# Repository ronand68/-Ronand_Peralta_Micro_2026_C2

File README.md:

# -Ronand_Peralta_Micro_2026_C2

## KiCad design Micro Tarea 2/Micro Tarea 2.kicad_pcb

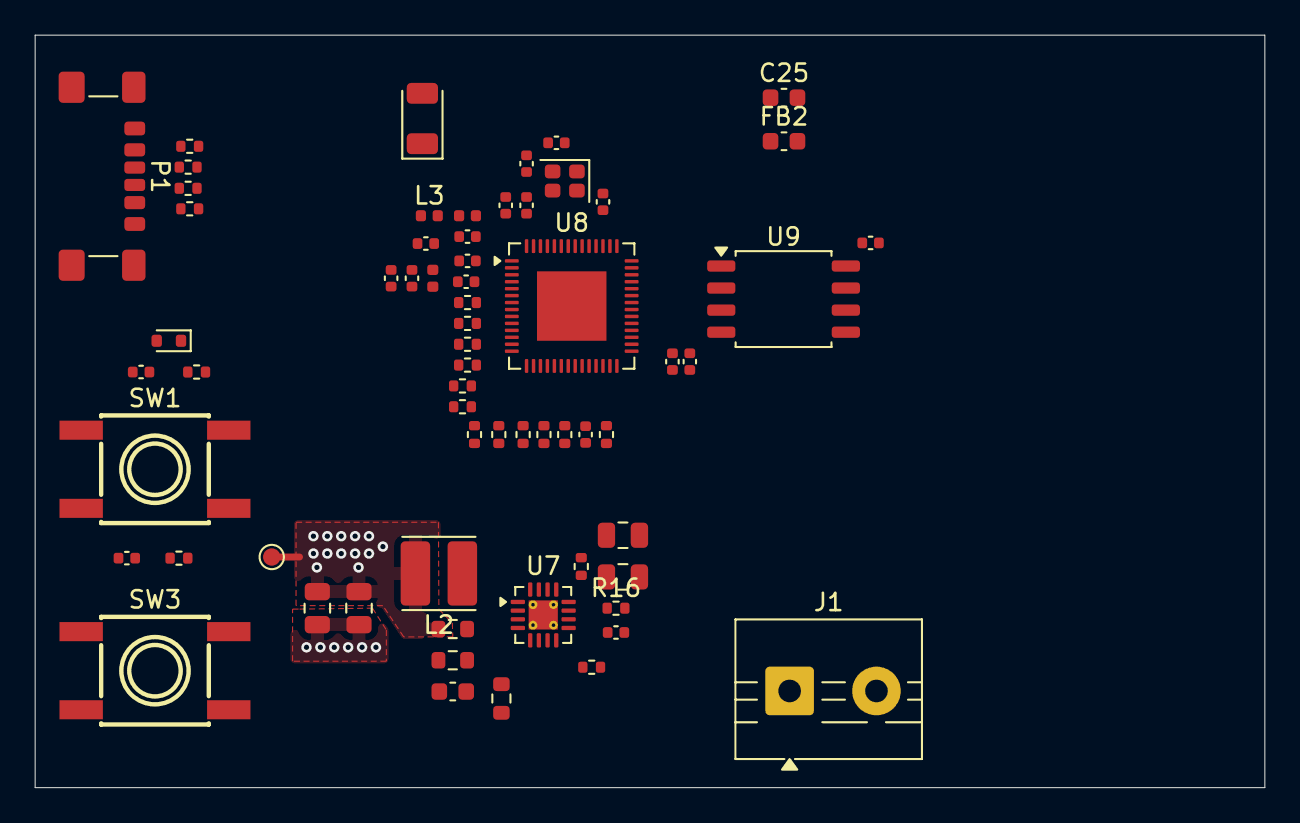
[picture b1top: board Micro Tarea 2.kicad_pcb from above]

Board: 4 copper layers, 70.8 x 43.3 mm, 64 parts (0 on the bottom side), 43 nets.

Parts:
AE1: 2450AT18A100E; Johanson_2450AT18x100
C14, C22: 22uF; C_0805_2012Metric
C15: 10uF; C_0805_2012Metric
C16: 10nF; C_0402_1005Metric
C21: 220pF; C_0603_1608Metric
C23: 100nF; C_0805_2012Metric
C24, C31, C35, C39: 1uF; C_0402_1005Metric
C25: 100nF; C_0603_1608Metric
C26, C27, C29: 12pF; C_0402_1005Metric
C28: 1.2pF; C_0402_1005Metric
C30, C32, C33, C34, C37, C38, C41: 100nF; C_0402_1005Metric
C36: 2.4pF; C_0402_1005Metric
C40: 10uF; C_0402_1005Metric
D5: LRB520S-30T1G; D_SOD-523
FB2: 120R; C_0603_1608Metric
J1: Screw_Terminal_01x02; TerminalBlock_MaiXu_MX126-5.0-02P_1x02_P5.00mm
L2: 2.2uH; L_Cenker_CKCS4020
L3: 3.3nH; L_0402_1005Metric
L4: 2.7nH; L_0402_1005Metric
L5: 2.2nH; L_0402_1005Metric
P1: USB_C_Plug_USB2.0; USB_C_Receptacle_GCT_USB4135-GF-A_6P_TopMnt_Horizontal
R2, R3: 22R; R_0402_1005Metric
R14, R15, R16: 100k; R_0402_1005Metric
R17: 49.9R; R_0603_1608Metric
R18: 68.1k; R_0603_1608Metric
R19: 22.1k; R_0603_1608Metric
R20, R21, R34, R35: 10k; R_0402_1005Metric
R22, R23, R24, R25, R26, R27, R28, R29, R30, R31: 0R; R_0402_1005Metric
R32, R33: 4.7k; R_0402_1005Metric
SW1, SW3: K2-1157SP-I4SW-04
TP6: TestPoint; TestPoint_Pad_D1.0mm
U7: TPS62130; VQFN-16-1EP_3x3mm_P0.5mm_EP1.68x1.68mm_ThermalVias
U8: ESP32-S3R8; QFN-56-1EP_7x7mm_P0.4mm_EP4x4mm
U9: W25Q128JVSIQ; SOIC-8_5.3x5.3mm_P1.27mm
Y1: 40MHz; Crystal_SMD_2016-4Pin_2.0x1.6mm

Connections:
+3V3: C22.1, C23.1, FB2.1, L2.2, R17.1, TP6.1 (1_1), U7.14 (VOS)
+5V: C14.1, C15.1, J1.1, P1.A9 (VBUS), P1.B9 (VBUS), R14.1, R15.1, R16.1, U7.10 (VIN), U7.11 (VIN), U7.12 (VIN)
/Untitled Sheet/SPI_CLK: U8.33 (SPICLK), U9.6 (CLK)
/Untitled Sheet/SPI_CS0: U8.32 (SPICS0), U9.1 (~CS)
/Untitled Sheet/SPI_D: U8.35 (SPID), U9.5 (DI/IO_{0})
/Untitled Sheet/SPI_HD: U8.30 (SPIHD), U9.7 (~HOLD/~RESET/IO_{3})
/Untitled Sheet/SPI_Q: U8.34 (SPIQ), U9.2 (DO/IO_{1})
/Untitled Sheet/SPI_WP: U8.31 (SPIWP), U9.3 (~WP/IO_{2})
ESP_3V3: C25.1, C30.1, C31.2, C32.2, C33.1, C34.1, C35.1, C38.1, C39.1, C40.1, C41.1, D5.1 (K), FB2.2, L5.2, R20.1, R21.1, R32.1, R33.1, U8.20 (VDD3P3_RTC), U8.29 (VDD_SPI), U8.46 (VDD3P3_CPU), U8.55 (VDDA1), U8.56 (VDDA2), U9.8 (VCC)
ESP_BOOT: C29.1, R21.2, SW3.1, SW3.2, U8.5 (GPIO0)
ESP_RST: C24.1, D5.2 (A), R20.2, SW1.1, SW1.2, U8.4 (CHIP_PU)
ESP_USB_N: R3.2, U8.25 (GPIO19)
ESP_USB_P: R2.2, U8.26 (GPIO20)
GND: C14.2, C15.2, C16.1, C22.2, C23.2, C24.2, C25.2, C26.1, C27.1, C29.2, C30.2, C33.2, C34.2, C35.2, C36.2, C37.2, C38.2, C39.2, C40.2, C41.2, J1.2, L4.1, P1.A12 (GND), P1.B12 (GND), P1.SH (SHIELD), R19.2, R34.2, R35.2, SW1.3, SW1.4, SW3.3, SW3.4, U7.6 (GND), U7.15 (GND), U7.16 (GND), U7.17 (GND), U8.57 (GND), U9.4 (GND), Y1.2, Y1.4
I2C_SCL: R33.2, U8.11 (GPIO6)
I2C_SDA: R32.2, U8.10 (GPIO5)
I2S2_MCLK: R26.2, R31.1
I2S_MCLK: R23.2, R31.2
unnamed: AE1.1, L3.1
unnamed: C21.1, R17.2, R18.1
unnamed: C28.1, L3.2, L4.2
unnamed: C31.1, C32.1
unnamed: C36.1, C37.1, L5.1, U8.2 (VDD3P3), U8.3 (VDD3P3)
unnamed: L2.1, U7.1 (SW), U7.2 (SW), U7.3 (SW)
unnamed: P1.A5 (CC), R34.1
unnamed: P1.B5 (VCONN), R35.1
unnamed: R14.2, U7.8 (DEF)
unnamed: R15.2, U7.13 (EN)
unnamed: C21.2, R18.2, R19.1, U7.5 (FB)
unnamed: R16.2, U7.4 (PG)
unnamed: C16.2, U7.9 (SS/TR)
unnamed: R29.1, U8.12 (GPIO7)
unnamed: R30.1, U8.13 (GPIO8)
unnamed: R23.1, U8.14 (GPIO9)
unnamed: R24.1, U8.15 (GPIO10)
unnamed: R25.1, U8.16 (GPIO11)
unnamed: R26.1, U8.17 (GPIO12)
unnamed: R27.1, U8.18 (GPIO13)
unnamed: R28.1, U8.19 (GPIO14)
unnamed: C28.2, U8.1 (LNA_IN)
unnamed: R22.2, U8.21 (XTAL_32K_P)
unnamed: C27.2, U8.53 (XTAL_N), Y1.1
unnamed: C26.2, U8.54 (XTAL_P), Y1.3

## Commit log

2026-06-11 Create LICENSE
2026-06-11 Subiendo tarea 1 y 2
2026-06-11 actualizando placa
